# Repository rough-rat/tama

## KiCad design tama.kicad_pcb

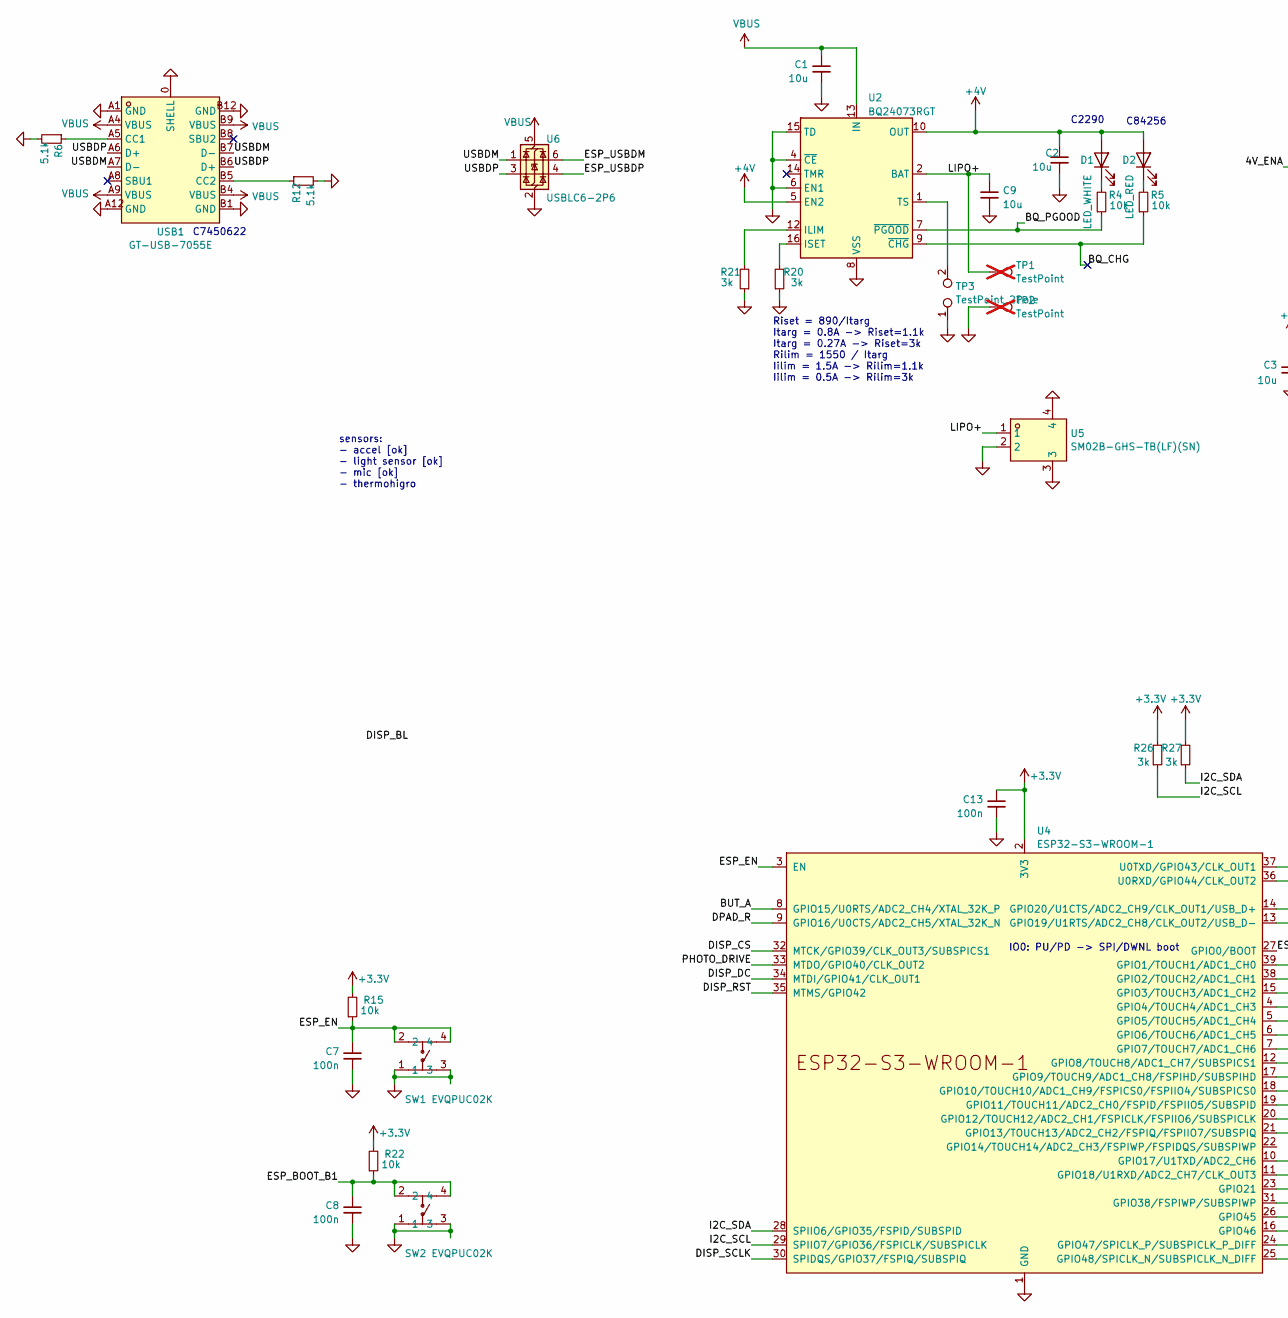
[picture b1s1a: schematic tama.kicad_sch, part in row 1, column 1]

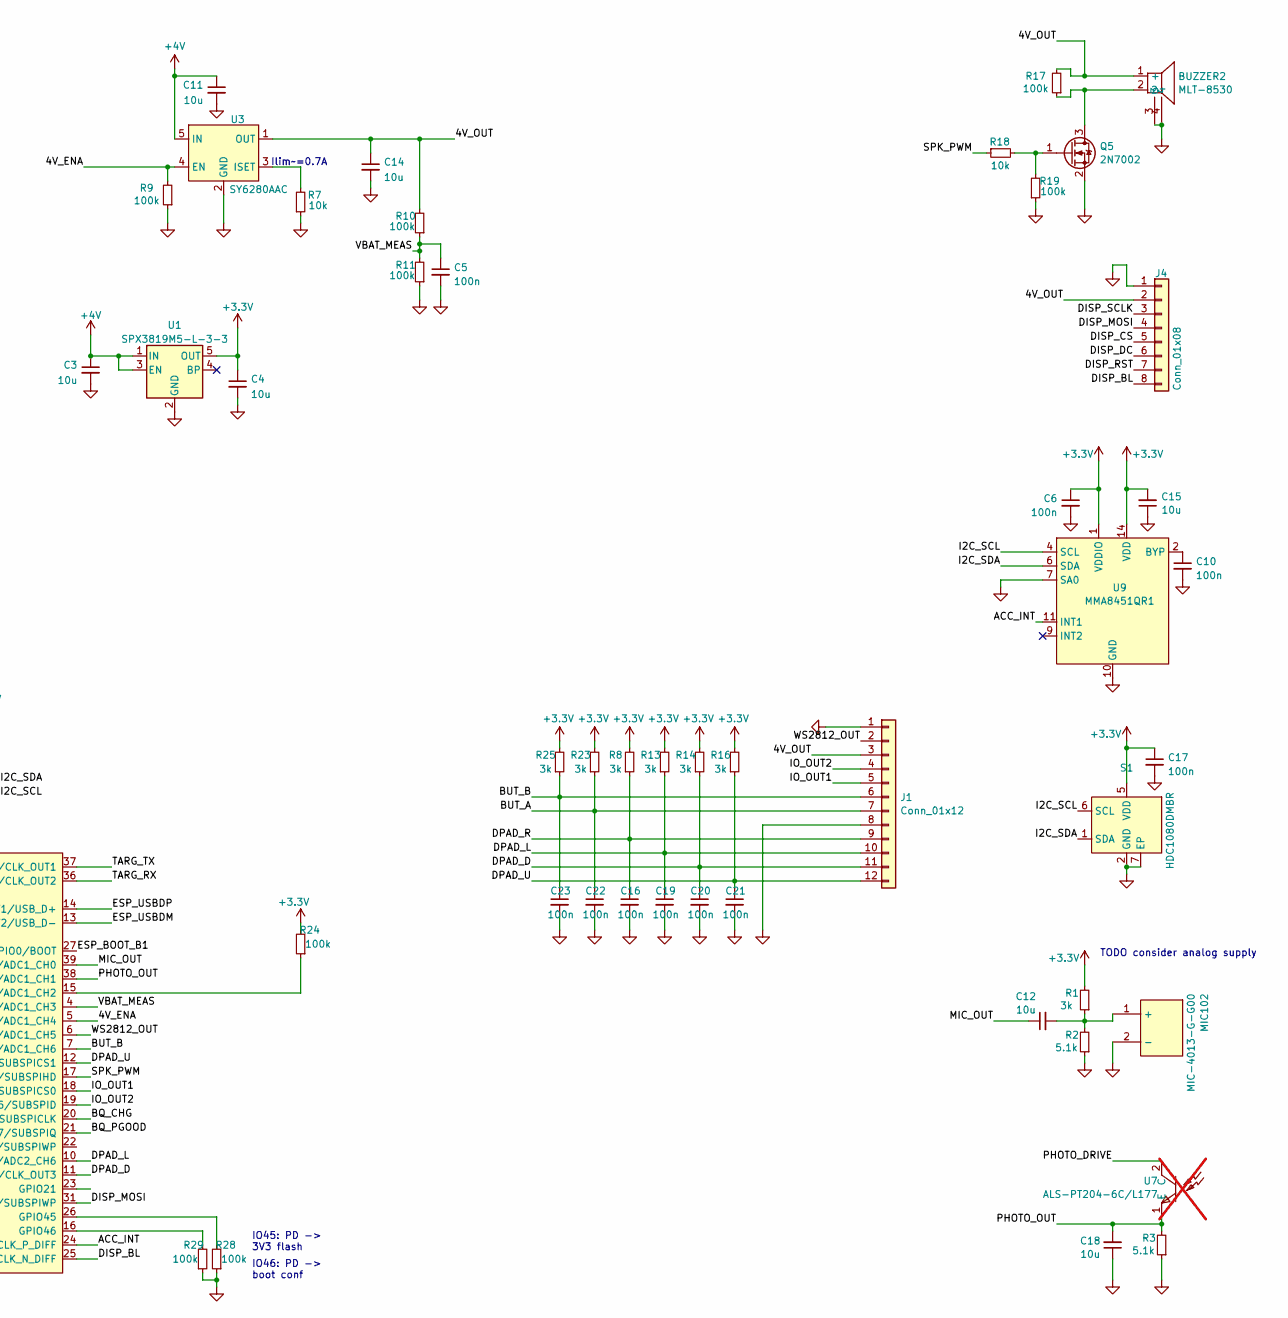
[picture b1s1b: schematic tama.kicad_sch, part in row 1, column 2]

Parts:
BUZZER2: MLT-8530; BUZ-SMD_4P-L8.5-W8.5-P8.50-BR; LCSC C94599
C1, C2, C3, C4, C9, C11, C12, C14, C15, C18: 10u; C_0603_1608Metric; LCSC C96446
C5, C6, C7, C8, C10, C13, C16, C17, C19, C20, C21, C22, C23: 100n; C_0402_1005Metric; LCSC C307331
D1: LED_WHITE; LED_0603_1608Metric; LCSC C2290
D2: LED_RED; LED_0603_1608Metric; LCSC C2286
J1: Conn_01x12; PinHeader_1x12_P2.54mm_Vertical
J4: Conn_01x08; PinHeader_1x08_P2.54mm_Vertical
MIC102: MIC-4013-G-G00; MIC-SMD_BD4.0-4013_SMDA; LCSC C42371093
Q5: 2N7002; SOT-23; LCSC C8545
R1, R8, R13, R14, R16, R20, R21, R23, R25, R26, R27: 3k; R_0402_1005Metric; LCSC C25890
R2, R3, R6, R12: 5.1k; R_0402_1005Metric; LCSC C25905
R4, R5, R7, R15, R18, R22: 10k; R_0402_1005Metric; LCSC C25744
R9, R10, R11, R17, R19, R24, R28, R29: 100k; R_0402_1005Metric; LCSC C25741
S1: HDC1080DMBR; SENSOR-SMD_HDC1080DMBR; LCSC C82227
SW1, SW2: EVQPUC02K; SW-SMD_EVQPUD02K; LCSC C79174
TP1, TP2: TestPoint; TestPoint_Pad_D1.5mm; not fitted
TP3: TestPoint_2Pole; PinHeader_1x02_P2.00mm_Vertical
U1: SPX3819M5-L-3-3; SOT-23-5; LCSC C5370980
U2: BQ24073RGT; VQFN-16-1EP_3x3mm_P0.5mm_EP1.6x1.6mm_ThermalVias; LCSC C15220
U3: SY6280AAC; SOT-23-5_L3.0-W1.7-P0.95-LS2.8-BL; LCSC C55136
U4: ESP32-S3-WROOM-1
U5: SM02B-GHS-TB(LF)(SN); CONN-SMD_SM02B-GHS-TB-LF-SN; LCSC C189893
U6: USBLC6-2P6; SOT-666; LCSC C2827693
U7: ALS-PT204-6C/L177; SENSOR-TH_BD4.0-P2.54-D0.5-1; LCSC C2936540; not fitted
U9: MMA8451QR1; QFN-16_L3.0-W3.0-P0.50-TL_FXOS8700CQR1; LCSC C118083
USB1: GT-USB-7055E; USB-C-SMD_GT-USB-7055E; LCSC C7450622

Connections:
+3.3V: C4.1, C6.1, C13.1, C15.2, C17.1, R1.2, R8.2, R13.2, R14.2, R15.2, R16.2, R22.2, R23.2, R24.2, R25.2, R26.2, R27.2, S1.5 (VDD), U1.5 (OUT), U4.2 (3V3), U9.1 (VDDIO), U9.14 (VDD)
+4V: C2.1, C3.1, C11.1, D1.2 (A), D2.2 (A), U1.1 (IN), U1.3 (EN), U2.5 (EN2), U2.10 (OUT), U2.11 (OUT), U3.5 (IN)
/4V_ENA: R9.2, U3.4 (EN), U4.5 (GPIO5/TOUCH5/ADC1_CH4)
/4V_OUT: BUZZER2.1 (+), C14.1, J1.3, J4.2, R10.2, R17.2, U3.1 (OUT)
/ACC_INT: U4.24 (GPIO47/SPICLK_P/SUBSPICLK_P_DIFF), U9.11 (INT1)
/BQ_CHG: R5.1, U2.9 (~CHG), U4.20 (GPIO12/TOUCH12/ADC2_CH1/FSPICLK/FSPIIO6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)
/BQ_PGOOD: R4.1, U2.7 (~PGOOD), U4.21 (GPIO13/TOUCH13/ADC2_CH2/FSPIQ/FSPIIO7/S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)
/BUT_A: C22.1, J1.7, R23.1, U4.8 (GPIO15/U0RTS/ADC2_CH4/XTAL_32K_P)
/BUT_B: C23.1, J1.6, R25.1, U4.7 (GPIO7/TOUCH7/ADC1_CH6)
/DISP_BL: J4.8, U4.25 (GPIO48/SPICLK_N/SUBSPICLK_N_DIFF)
/DISP_CS: J4.5, U4.32 (MTCK/GPIO39/CLK_OUT3/SUBSPICS1)
/DISP_DC: J4.6, U4.34 (MTDI/GPIO41/CLK_OUT1)
/DISP_MOSI: J4.4, U4.31 (GPIO38/FSPIWP/SUBSPIWP)
/DISP_RST: J4.7, U4.35 (MTMS/GPIO42)
/DISP_SCLK: J4.3, U4.30 (SPIDQS/GPIO37/FSPIQ/SUBSPIQ)
/DPAD_D: C20.1, J1.11, R14.1, U4.11 (GPIO18/U1RXD/ADC2_CH7/CLK_OUT3)
/DPAD_L: C19.1, J1.10, R13.1, U4.10 (GPIO17/U1TXD/ADC2_CH6)
/DPAD_R: C16.1, J1.9, R8.1, U4.9 (GPIO16/U0CTS/ADC2_CH5/XTAL_32K_N)
/DPAD_U: C21.1, J1.12, R16.1, U4.12 (GPIO8/TOUCH8/ADC1_CH7/SUBSPICS1)
/ESP_BOOT_B1: C8.1, R22.1, SW2.2, SW2.4, U4.27 (GPIO0/BOOT)
/ESP_EN: C7.1, R15.1, SW1.2, SW1.4, U4.3 (EN)
/ESP_USBDM: U4.13 (GPIO19/U1RTS/ADC2_CH8/CLK_OUT2/USB_D-), U6.6 (I/O1)
/ESP_USBDP: U4.14 (GPIO20/U1CTS/ADC2_CH9/CLK_OUT1/USB_D+), U6.4 (I/O2)
/I2C_SCL: R26.1, S1.6 (SCL), U4.29 (SPIIO7/GPIO36/FSPICLK/SUBSPICLK), U9.4 (SCL)
/I2C_SDA: R27.1, S1.1 (SDA), U4.28 (SPIIO6/GPIO35/FSPID/SUBSPID), U9.6 (SDA)
/IO_OUT1: J1.5, U4.18 (GPIO10/TOUCH10/ADC1_CH9/FSPICS0/FSPIIO4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)
/IO_OUT2: J1.4, U4.19 (GPIO11/TOUCH11/ADC2_CH0/FSPID/FSPIIO5/S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)
/LIPO+: C9.1, TP1.1, U2.2 (BAT), U2.3 (BAT), U5.1
/MIC_OUT: C12.1, U4.39 (GPIO1/TOUCH1/ADC1_CH0)
/PHOTO_DRIVE: U4.33 (MTDO/GPIO40/CLK_OUT2), U7.2 (C)
/PHOTO_OUT: C18.2, R3.2, U4.38 (GPIO2/TOUCH2/ADC1_CH1), U7.1 (E)
/SPK_PWM: R18.1, U4.17 (GPIO9/TOUCH9/ADC1_CH8/FSPIHD/SUBSPIHD)
/TARG_RX: U4.36 (U0RXD/GPIO44/CLK_OUT2)
/TARG_TX: U4.37 (U0TXD/GPIO43/CLK_OUT1)
/USBDM: U6.1 (I/O1), USB1.A7 (D-), USB1.B7 (D-)
/USBDP: U6.3 (I/O2), USB1.A6 (D+), USB1.B6 (D+)
/VBAT_MEAS: C5.1, R10.1, R11.2, U4.4 (GPIO4/TOUCH4/ADC1_CH3)
/WS2812_OUT: J1.2, U4.6 (GPIO6/TOUCH6/ADC1_CH5)
GND: BUZZER2.3, BUZZER2.4, C1.2, C2.2, C3.2, C4.2, C5.2, C6.2, C7.2, C8.2, C9.2, C10.2, C11.2, C13.2, C14.2, C15.1, C16.2, C17.2, C18.1, C19.2, C20.2, C21.2, C22.2, C23.2, J1.1, J1.8, J4.1, MIC102.2 (-), Q5.2 (S), R2.1, R3.1, R6.2, R7.1, R9.1, R11.1, R12.2, R19.1, R20.1, R21.1, R28.1, R29.1, S1.2 (GND), S1.7 (EP), SW1.1, SW1.3, SW2.1, SW2.3, TP2.1, TP3.1, U1.2 (GND), U2.4 (~CE), U2.6 (EN1), U2.8 (VSS), U2.15 (TD), U2.17 (VSS), U3.2 (GND), U4.1 (GND), U4.40 (GND), U4.41 (GND), U5.2, U5.3, U5.4, U6.2 (GND), U9.5 (GND), U9.7 (SA0), U9.10 (GND), U9.12 (GND), USB1.0 (SHELL), USB1.A1 (GND), USB1.A12 (GND), USB1.B1 (GND), USB1.B12 (GND)
unnamed: D1.1 (K), R4.2
unnamed: D2.1 (K), R5.2
unnamed: C12.2, MIC102.1 (+), R1.1, R2.2
unnamed: BUZZER2.2, Q5.3 (D), R17.1
unnamed: Q5.1 (G), R18.2, R19.2
unnamed: R21.2, U2.12 (ILIM)
unnamed: R20.2, U2.16 (ISET)
unnamed: TP3.2, U2.1 (TS)
unnamed: R7.2, U3.3 (ISET)
unnamed: R24.1, U4.15 (GPIO3/TOUCH3/ADC1_CH2)
unnamed: R28.2, U4.26 (GPIO45)
unnamed: R29.2, U4.16 (GPIO46)
unnamed: C10.1, U9.2 (BYP)
unnamed: R6.1, USB1.A5 (CC1)
unnamed: R12.1, USB1.B5 (CC2)
VBUS: C1.1, U2.13 (IN), U6.5 (VBUS), USB1.A4 (VBUS), USB1.A9 (VBUS), USB1.B4 (VBUS), USB1.B9 (VBUS)

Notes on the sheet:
C84256
Riset = 890/Itarg Itarg = 0.8A -> Riset=1.1k Itarg = 0.27A -> Riset=3k Rilim = 1550 / Itarg Iilim = 1.5A -> Rilim=1.1k Iilim = 0.5A -> Rilim=3k
IO45: PD -> 3V3 flash
IO46: PD -> boot conf
C7450622
sensors: - accel [ok] - light sensor [ok] - mic [ok] - thermohigro
IO0: PU/PD -> SPI/DWNL boot
TODO consider analog supply
Ilim~=0.7A
C2290

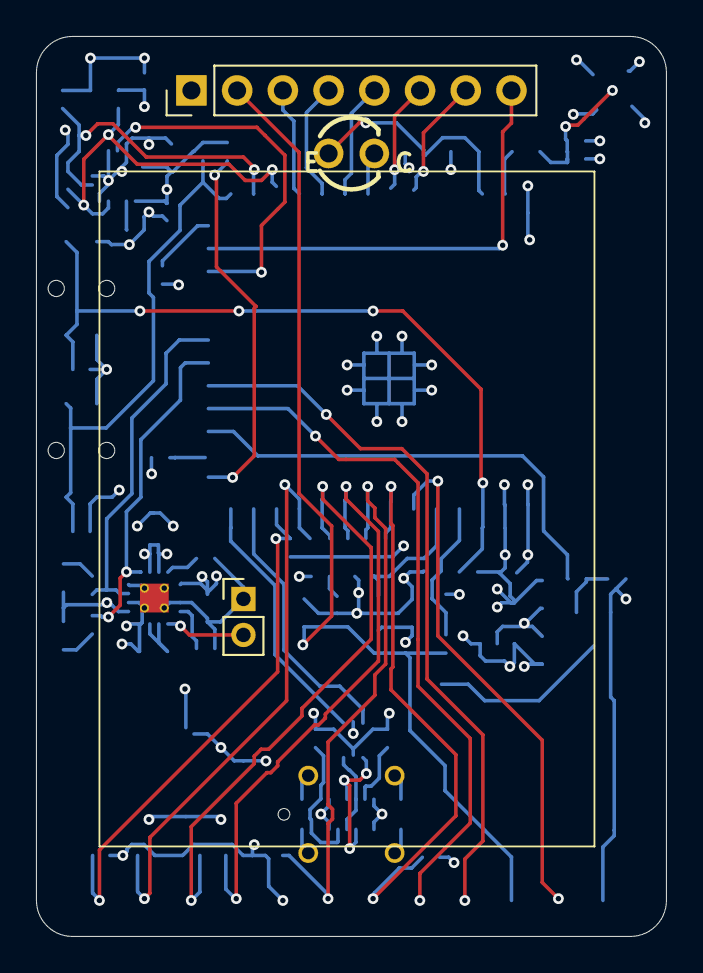
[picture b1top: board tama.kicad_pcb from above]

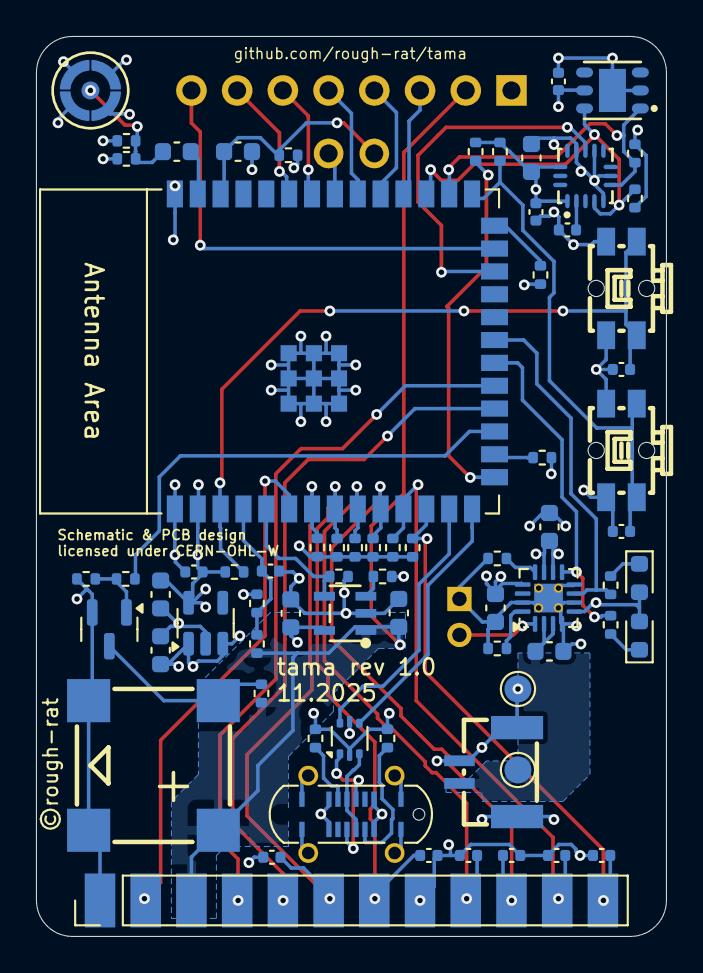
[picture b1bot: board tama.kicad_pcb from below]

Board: 4 copper layers, 35.0 x 50.0 mm, 74 parts (71 on the bottom side), 53 nets.

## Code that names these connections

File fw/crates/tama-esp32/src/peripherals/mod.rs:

pub mod adc_bus;
mod button_driver;
mod display_driver;
mod power_control;
pub mod pwm_bus;
mod sensor_driver;
pub mod sensors_i2c;

pub use adc_bus::{AdcBus, AdcPins};
pub use button_driver::ButtonDriver;
pub use display_driver::DisplayDriver;
pub use power_control::{PowerControl, PowerPeripherals};
pub use pwm_bus::{PwmBus, PwmPeripherals, BacklightControl};
pub use sensor_driver::SensorDriver;

use esp_idf_hal::adc;
use esp_idf_hal::gpio::{AnyInputPin, AnyIOPin, AnyOutputPin};
use esp_idf_hal::i2c::I2C0;
use esp_idf_hal::peripherals::Peripherals;
use esp_idf_hal::spi;

pub struct SystemPeripherals<SPI> {
    pub adc1: adc::ADC1,
    pub adc_pins: AdcPins,
    pub buttons: ButtonPeripherals,
    pub display: DisplaySpiPeripherals<SPI>,
    pub power: PowerPeripherals,
    pub pwm: PwmPeripherals<
        esp_idf_hal::ledc::TIMER0,
        esp_idf_hal::ledc::CHANNEL0,
        esp_idf_hal::ledc::CHANNEL1,
        esp_idf_hal::gpio::Gpio48,
        esp_idf_hal::gpio::Gpio9,
    >,
    pub sensors: SensorPeripherals,
}

/// Button GPIO pins
/// Active low (directly connected to GND when pressed)
pub struct ButtonPeripherals {
    pub btn_a: AnyInputPin,    // GPIO15
    pub btn_b: AnyInputPin,    // GPIO7
    pub btn_up: AnyInputPin,   // GPIO8
    pub btn_down: AnyInputPin, // GPIO18
    pub btn_left: AnyInputPin, // GPIO17
    pub btn_right: AnyInputPin,// GPIO16
    pub btn_boot: AnyInputPin, // GPIO0 (BOOT button)
}

/// Sensor peripherals for light, mic, and I2C sensors
/// Note: ADC pins are handled by AdcPins, battery is handled by PowerPeripherals
pub struct SensorPeripherals {
    pub light_sensor_enable: AnyOutputPin,          // GPIO40 - Light sensor enable
    // I2C sensor bus
    pub i2c: I2C0,
    pub i2c_sda: AnyIOPin,                         // GPIO35
    pub i2c_scl: AnyIOPin,                         // GPIO36
    pub acc_int1: AnyInputPin,                     // GPIO47 - accelerometer interrupt
}

pub struct DisplayControlPeripherals {
    pub dc: AnyOutputPin,
    pub rst: AnyOutputPin,
}

pub struct DisplaySpiPeripherals<SPI> {
    pub control: DisplayControlPeripherals,
    pub spi: SPI,
    pub sclk: AnyOutputPin,
    pub sdo: AnyOutputPin,
    pub sdi: AnyInputPin,
    pub cs: AnyOutputPin,
}

impl SystemPeripherals<spi::SPI2> {
    pub fn take() -> Self {
        let peripherals = Peripherals::take().unwrap();

        SystemPeripherals {
            adc1: peripherals.adc1,
            adc_pins: AdcPins {
                battery_pin: peripherals.pins.gpio4,
                light_pin: peripherals.pins.gpio2,
                mic_pin: peripherals.pins.gpio1,
            },
            buttons: ButtonPeripherals {
                btn_a: peripherals.pins.gpio15.into(),
                btn_b: peripherals.pins.gpio7.into(),
                btn_up: peripherals.pins.gpio8.into(),
                btn_down: peripherals.pins.gpio18.into(),
                btn_left: peripherals.pins.gpio17.into(),
                btn_right: peripherals.pins.gpio16.into(),
                btn_boot: peripherals.pins.gpio0.into(),
            },
            power: PowerPeripherals {
                peripheral_power_pin: peripherals.pins.gpio5.into(),
            },
            pwm: PwmPeripherals {
                timer: peripherals.ledc.timer0,
                backlight_channel: peripherals.ledc.channel0,
                backlight_pin: peripherals.pins.gpio48,
                buzzer_channel: peripherals.ledc.channel1,
                buzzer_pin: peripherals.pins.gpio9,
            },
            sensors: SensorPeripherals {
                light_sensor_enable: peripherals.pins.gpio40.into(),
                // I2C sensor bus
                i2c: peripherals.i2c0,
                i2c_sda: peripherals.pins.gpio35.into(),
                i2c_scl: peripherals.pins.gpio36.into(),
                acc_int1: peripherals.pins.gpio47.into(),
            },
            display: DisplaySpiPeripherals {
                control: DisplayControlPeripherals {
                    dc: peripherals.pins.gpio41.into(),
                    rst: peripherals.pins.gpio39.into(),
                },
                spi: peripherals.spi2,
                sclk: peripherals.pins.gpio37.into(),
                sdo: peripherals.pins.gpio38.into(),
                sdi: peripherals.pins.gpio14.into(),
                cs: peripherals.pins.gpio42.into(),
            },
        }
    }
}

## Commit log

2025-10-21 select sensors, initial pcb
2025-11-08 basic engine setup
2025-11-08 start flappy bird implementation
2025-11-08 add button handling and player movement
2025-11-09 implement collisions
2025-11-09 add scene switching
2025-11-09 add docs
2025-11-09 add init screen
2025-11-09 add sensors interface
2025-11-10 add shitty buzzer poc
2025-11-10 add beeps to flappy
2025-11-10 tui for sensor mocking and logs
2025-11-17 integrate esp32 target
2025-11-18 split render and display write to threads
2025-11-19 constant fps and stuff
2025-11-28 add new schematic to git
2025-11-29 fix sch pin error, add pins for tama pcb to code
2025-11-29 add transparent images
2025-11-30 add some peripherals handling
2025-11-30 add i2c sensors stub
2025-11-30 move ADC logic to separate module, add power controller stub
2025-11-30 add log capture for exporting log access to engine
2025-11-30 integrate esp buzzer to engine
2025-12-29 wip: simple menu
2025-12-29 refactor sensors
2025-12-29 context to draw
2025-12-31 rounded corners in simulator
2025-12-31 add time mock

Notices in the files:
tama.kicad_pcb:
©rough-rat
licensed under CERN-OHL-W
